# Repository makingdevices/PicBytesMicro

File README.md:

<!-- Improved compatibility of back to top link: See: https://github.com/othneildrew/Best-README-Template/pull/73 -->

<!--
*** Thanks for checking out the Best-README-Template. If you have a suggestion
*** that would make this better, please fork the repo and create a pull request
*** or simply open an issue with the tag "enhancement".
*** Don't forget to give the project a star!
*** Thanks again! Now go create something AMAZING! :D
-->

<!-- PROJECT SHIELDS -->
<!--
*** I'm using markdown "reference style" links for readability.
*** Reference links are enclosed in brackets [ ] instead of parentheses ( ).
*** See the bottom of this document for the declaration of the reference variables
*** for contributors-url, forks-url, etc. This is an optional, concise syntax you may use.
*** https://www.markdownguide.org/basic-syntax/#reference-style-links
-->
[![Instagram][ig-shield]][ig-url]
[![PCBWAY][sponsor-shield]][sponsor-url]
[![Stargazers][stars-shield]][stars-url]
[![Issues][issues-shield]][issues-url]
[![LinkedIn][linkedin-shield]][linkedin-url]

<!-- PROJECT LOGO -->
<br />
<div align="center">

<h3 align="center">Making Devices</h3>

  <p align="center">
    Open Source projects where we struggle with engineering, electronics, coding and who knows what else... Pic Bytes Micro is a 8-bit console based in the PIC18F4550 with an analog LED matrix as the screen.
  </p>
</div>

<!-- TABLE OF CONTENTS -->
<details>
  <summary>Table of Contents</summary>
  <ol>
    <li>
      <a href="#about-the-project">About The Project</a>
      <ul>
        <li><a href="#built-with">Built With</a></li>
      </ul>
    </li>
    <li>
      <a href="#Build-one">Build one</a>
      <ul>
      </ul>
    </li>
    <li><a href="#usage">Usage</a></li>
    <li><a href="#roadmap">Roadmap</a></li>
    <li><a href="#license">License</a></li>
    <li><a href="#contact">Contact</a></li>
    <li><a href="#Sponsor">Sponsor</a></li>
  </ol>
</details>

<!-- ABOUT THE PROJECT -->
## About The Project

[![Bytes Counter Shot][product-screenshot]](https://makingdevices.com/PicBytesMicro)

Pic Bytes Micro was born to explore the capabilities of C language inside the PIC18F4550, as I wanted to test if the 8bit microcontroller was able to run some old games such tetris, snake or arkanoid. To maintain the old-fashion look of the project, the screen is made by 16x10 matrix of LEDs, controlled by individual transistors and the IO pins of the PIC. In addition, sounds and a rechargable battery will be added to the device.

<p align="right">(<a href="#readme-top">back to top</a>)</p>

### Built With

[![Microcontroller][PIC]][PIC-url]
[![MPLAB C][MPLAB-C]][MPLAB-C-url]
[![Kicad][kicad-shield]][kicad-url]
[![SPONSOR][wurth-icon]][sponsor-url-wurth]
[![SPONSOR][sponsor-icon]][sponsor-url]

<p align="right">(<a href="#readme-top">back to top</a>)</p>

<!-- GETTING STARTED -->

## Build one
The project is finished and no further development will be made. The device is safe, stable and It was tested. 

1. Get the gerber files for the latest version: [V1.25](/Gerber/PicBytesMicroV1.25.zip) 
2. Send them to a PCB manufacturer ([Our Sponsor is PCBWAY][sponsor-url])
3. You can read the [schematics](/output_files/PicBytesMicro_schematic_V1.25.pdf) 
4. [The firmware is available on the repo](/Simulation%26Firmware) 
5. For most of the components, you can reach to [Würth Elektronik, our sponsor for electronic components](https://www.we-online.com/en) 

<p align="right">(<a href="#readme-top">back to top</a>)</p>

<!-- USAGE EXAMPLES -->
## Usage

Instructions of use:

- When turn on, a menu is shown to select between the available games.
- Once you have played a game, a score board will appear everytime you open the game.
- You have a setting menu to turn-off the init splash and the sound.
- If you leave the console one minute without touching the buttons, it will turn into sleep mode.
- Enjoy!

<p align="right">(<a href="#readme-top">back to top</a>)</p>

<!-- ROADMAP -->
## Roadmap

- [x] Solder the prototype
- [x] Test the LCD of the prototype
- [x] Design a PCB
  - [x] Add rechargeable battery
  - [x] Add USB communication if possible.
  - [x] Add sound control with the buzzers
  - [x] Develop Snake game
  - [x] Develop Tetris game
  - [x] Develop Arkanoid game
  - [x] Score board
  - [x] Sleep Mode
- [x] Validate the design

See the [open issues](https://github.com/makingdevices/PicBytesMicro/issues) for a full list of proposed features (and known issues).

State: Project <b>FINISHED</b> - 22/05/2024

Priority: <b>Medium</b>

<p align="right">(<a href="#readme-top">back to top</a>)</p>

<!-- LICENSE -->
## License

Distributed under three licenses:
- [Hardware](/License/HW_cern_ohl_s_v2.pdf)
- [Software](/License/SW_GPLv3.0.txt)
- [Documentation](/License/Documentation_CC-BY-SA-4.0.txt)

OSHWA License: [ES000047](https://certification.oshwa.org/es000047.html)

[![GPL v3 License][license-shield]][license-url] 
<p align="right">(<a href="#readme-top">back to top</a>)</p>

<!-- CONTACT -->
## Contact

Making Devices - [@MakingDevices](https://www.instagram.com/makingdevices/)

Project Link: [https://github.com/makingdevices/PicBytesMicro](https://github.com/makingdevices/PicBytesMicro/)

Other Links: [LinkTree](https://makingdevices.com/links/)

<!-- Sponsor -->
## Sponsors - Würth Elektronik

[Wurth Elektronik](https://www.we-online.com/en) is one of the leading manufacturers of electronic and electromechanical components. The best I can say about them is to show you some pictures: All the LEDs from the board are from them. They also have buttons, resistors and capacitors that we use in all our PCBs. They also have some design kits with a lifetime refill which are amazing for makers and business so you can prototype on the go with a huge variety of components!

[![Sponsor Shot][sponsor-wurth-1]][sponsor-url-wurth]
[![Sponsor Shot][sponsor-wurth-3]][sponsor-url-wurth]

## PCBWAY

[PCBWAY](https://www.pcbway.com/?from=makingdevices) is the most professional PCB manufacturer for prototyping and low-volume production to work with in the world. With more than a decade in the field, They are committed to meeting the needs of their customers from different industries in terms of quality, delivery, cost-effectiveness and any other demanding requests. As Sponsor of Making Devices, they will be in charge of all the PCBs for MDV, allowing both of us to grow together in a long term partnership. We hope you take them into account for your both personal and professional prototypes or products.

[![Sponsor Shot][sponsor-pcb-1]][sponsor-url]
[![Sponsor Shot][sponsor-pcb-2]][sponsor-url]

<p align="right">(<a href="#readme-top">back to top</a>)</p>

<!-- MARKDOWN LINKS & IMAGES -->
<!-- https://www.markdownguide.org/basic-syntax/#reference-style-links -->
[contributors-shield]: https://img.shields.io/github/contributors/makingdevices/PicBytesMicro.svg?style=for-the-badge
[contributors-url]: https://github.com/makingdevices/PicBytesMicro/graphs/contributors
[forks-shield]: https://img.shields.io/github/forks/makingdevices/PicBytesMicro.svg?style=for-the-badge
[forks-url]: https://github.com/makingdevices/PicBytesMicro/network/members
[stars-shield]: https://img.shields.io/github/stars/makingdevices/PicBytesMicro.svg?style=for-the-badge
[stars-url]: https://github.com/makingdevices/PicBytesMicro/stargazers
[issues-shield]: https://img.shields.io/github/issues/makingdevices/PicBytesMicro.svg?style=for-the-badge
[issues-url]: https://github.com/makingdevices/PicBytesMicro/issues
[license-shield]: /images/license.png
[license-url]: https://github.com/makingdevices/PicBytesMicro/tree/main/License
[linkedin-shield]: https://img.shields.io/badge/-LinkedIn-black.svg?style=for-the-badge&logo=linkedin&colorB=555
[linkedin-url]: https://www.linkedin.com/company/making-devices/
[sponsor-shield]: https://img.shields.io/badge/SPONSOR-PCBWAY-black.svg?style=for-the-badge&colorB=1200
[sponsor-url]: https://www.pcbway.com/?from=makingdevices
[sponsor-screenshot]: /images/PCB_sponsor.png
[sponsor-pcb-1]: /images/picbytesmicro_pcb1.jpg
[sponsor-pcb-2]: /images/picbytesmicro_pcb2.jpg
[sponsor-wurth-1]: /images/wurth_1.JPG
[sponsor-wurth-3]: /images/wurth_3.jpg
[sponsor-url-wurth]: https://www.we-online.com/en
[product-screenshot]: images/screenshot.jpg
[PIC]: https://img.shields.io/badge/PIC18LF4550-000000?style=for-the-badge
[PIC-url]: https://ww1.microchip.com/downloads/aemDocuments/documents/OTH/ProductDocuments/DataSheets/39632e.pdf
[kicad-shield]: https://img.shields.io/badge/kicad-0b03fc?style=for-the-badge&logo=kicad&logoColor=white
[kicad-url]: https://www.kicad.org/
[YT-screenshot]: images/YT_assembly.PNG
[sponsor-icon]:  https://img.shields.io/badge/-PCBWAY-black.svg?style=for-the-badge&colorB=1200
[ig-shield]: https://img.shields.io/badge/instagram-a83297?style=for-the-badge&logo=instagram&logoColor=white
[ig-url]: https://www.instagram.com/makingdevices/
[MPLAB-C]: https://img.shields.io/badge/MPLAB%20C18-DD0031?style=for-the-badge&logo=C&logoColor=white
[wurth-icon]: https://img.shields.io/badge/Wurth%20elektronik-FF0031?style=for-the-badge&logoColor=white
[MPLAB-C-url]: https://www.microchip.com/en-us/development-tool/SW006011
[Svelte.dev]: https://img.shields.io/badge/Svelte-4A4A55?style=for-the-badge&logo=svelte&logoColor=FF3E00
[Svelte-url]: https://svelte.dev/
[Laravel.com]: https://img.shields.io/badge/Laravel-FF2D20?style=for-the-badge&logo=laravel&logoColor=white
[Laravel-url]: https://laravel.com
[Bootstrap.com]: https://img.shields.io/badge/Bootstrap-563D7C?style=for-the-badge&logo=bootstrap&logoColor=white
[Bootstrap-url]: https://getbootstrap.com
[JQuery.com]: https://img.shields.io/badge/jQuery-0769AD?style=for-the-badge&logo=jquery&logoColor=white
[JQuery-url]: https://jquery.com

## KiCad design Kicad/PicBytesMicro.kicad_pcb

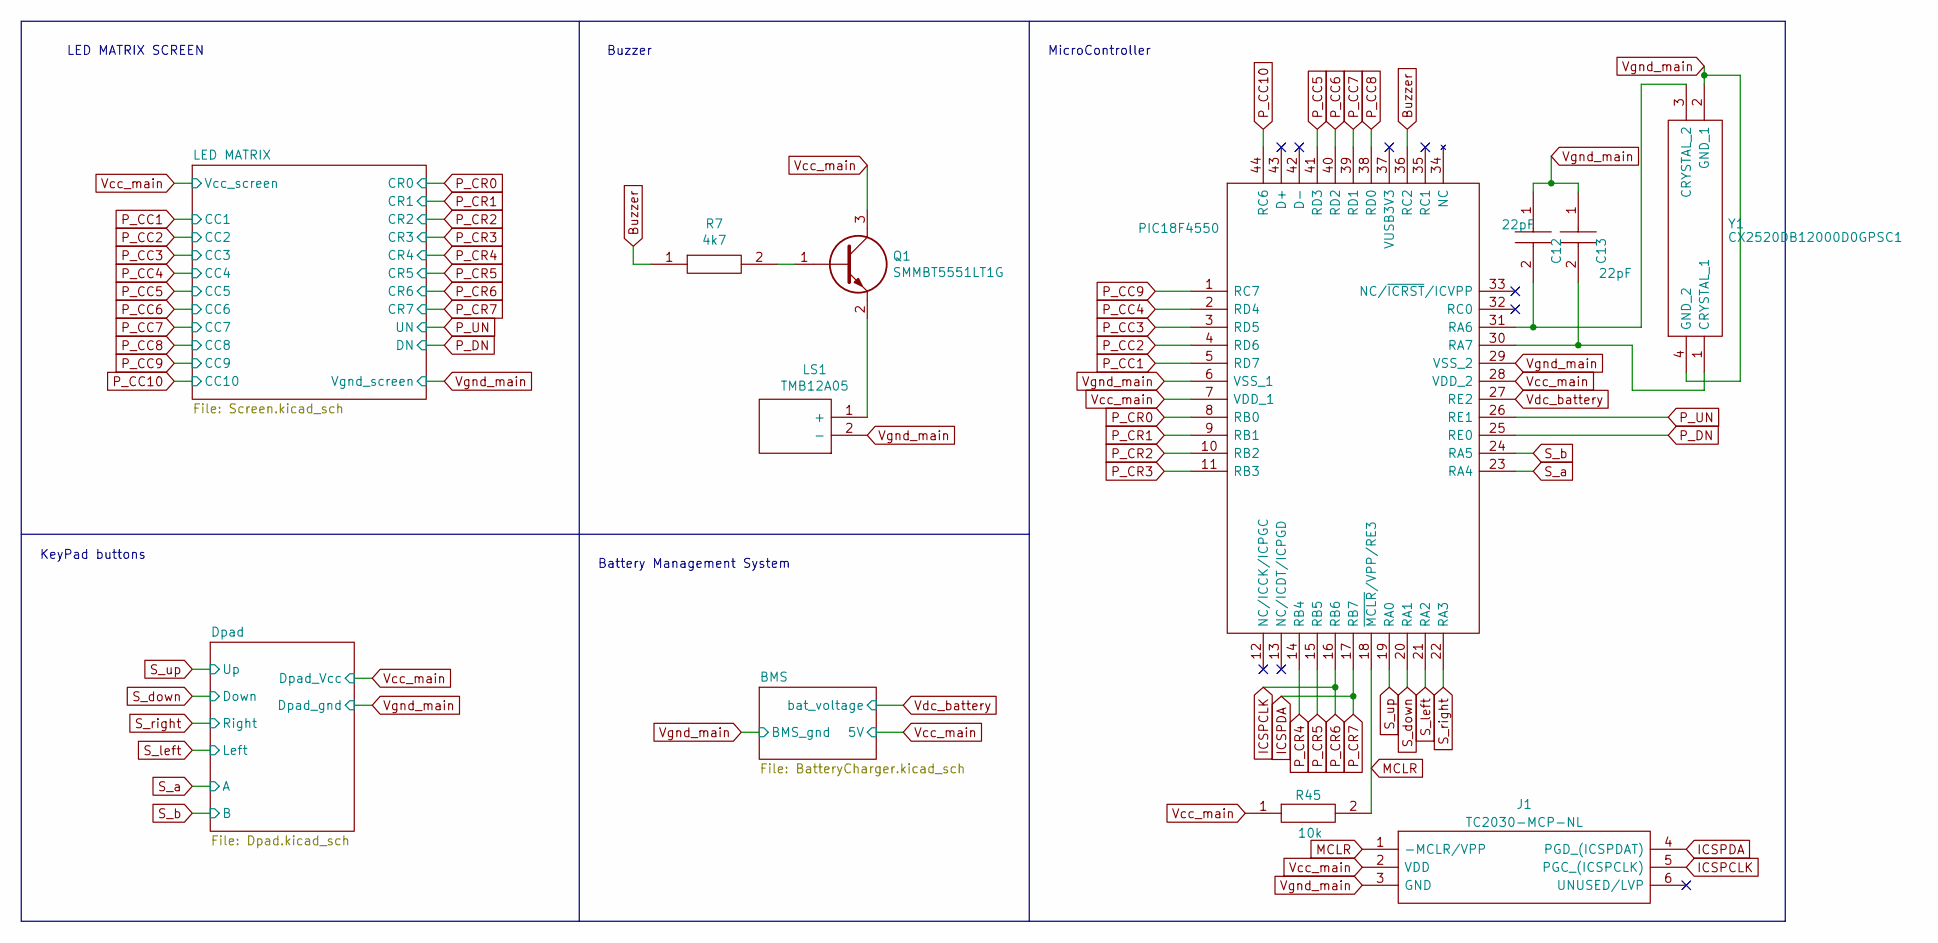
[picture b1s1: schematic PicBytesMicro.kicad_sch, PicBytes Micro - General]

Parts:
C12, C13: 22pF; CAPC2012X145N; Manufacturer_Part_Number GCG21BR71H154KA01K
J1: TC2030-MCP-NL; Manufacturer_Part_Number TC2030-MCP-NL
LS1: TMB12A05; Manufacturer_Part_Number TMB12A05
PIC18F4550: PIC18F4550-I_PT; QFP80P1200X1200X120-44N; Manufacturer_Part_Number PIC18F45K50-I/PT
Q1: SMMBT5551LT1G; SOT96P237X111-3N; Manufacturer_Part_Number SMMBT5551LT1G
R7: 4k7; RESC2012X65N; Manufacturer_Part_Number KTR10EZPF4220
R45: 10k; RESC2012X65N; Manufacturer_Part_Number KTR10EZPF4220
Y1: CX2520DB12000D0GPSC1; Manufacturer_Part_Number CX2520DB12000D0GPSC1

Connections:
Buzzer: PIC18F4550.36 (RC2), R7.1
ICSPCLK: J1.5 (PGC_(ICSPCLK)), PIC18F4550.16 (RB6); also elsewhere on the board
ICSPDA: J1.4 (PGD_(ICSPDAT)), PIC18F4550.17 (RB7); also elsewhere on the board
MCLR: J1.1 (-MCLR/VPP), PIC18F4550.18 (~MCLR/VPP/RE3), R45.2
unnamed: LS1.1 (+), Q1.2
unnamed: C12.2, PIC18F4550.31 (RA6), Y1.3 (CRYSTAL_2)
unnamed: C13.2, PIC18F4550.30 (RA7), Y1.1 (CRYSTAL_1)
unnamed: Q1.1, R7.2
P_CC1: PIC18F4550.5 (RD7); also elsewhere on the board
P_CC2: PIC18F4550.4 (RD6); also elsewhere on the board
P_CC3: PIC18F4550.3 (RD5); also elsewhere on the board
P_CC4: PIC18F4550.2 (RD4); also elsewhere on the board
P_CC5: PIC18F4550.41 (RD3); also elsewhere on the board
P_CC6: PIC18F4550.40 (RD2); also elsewhere on the board
P_CC7: PIC18F4550.39 (RD1); also elsewhere on the board
P_CC8: PIC18F4550.38 (RD0); also elsewhere on the board
P_CC9: PIC18F4550.1 (RC7); also elsewhere on the board
P_CC10: PIC18F4550.44 (RC6); also elsewhere on the board
P_CR0: PIC18F4550.8 (RB0); also elsewhere on the board
P_CR1: PIC18F4550.9 (RB1); also elsewhere on the board
P_CR2: PIC18F4550.10 (RB2); also elsewhere on the board
P_CR3: PIC18F4550.11 (RB3); also elsewhere on the board
P_CR4: PIC18F4550.14 (RB4); also elsewhere on the board
P_CR5: PIC18F4550.15 (RB5); also elsewhere on the board
P_DN: PIC18F4550.25 (RE0); also elsewhere on the board
P_UN: PIC18F4550.26 (RE1); also elsewhere on the board
S_a: PIC18F4550.23 (RA4); also elsewhere on the board
S_b: PIC18F4550.24 (RA5); also elsewhere on the board
S_down: PIC18F4550.20 (RA1); also elsewhere on the board
S_left: PIC18F4550.21 (RA2); also elsewhere on the board
S_right: PIC18F4550.22 (RA3); also elsewhere on the board
S_up: PIC18F4550.19 (RA0); also elsewhere on the board
Vcc_main: J1.2 (VDD), PIC18F4550.7 (VDD_1), PIC18F4550.28 (VDD_2), Q1.3, R45.1; also elsewhere on the board
Vdc_battery: PIC18F4550.27 (RE2); also elsewhere on the board
Vgnd_main: C12.1, C13.1, J1.3 (GND), LS1.2 (-), PIC18F4550.6 (VSS_1), PIC18F4550.29 (VSS_2), Y1.2 (GND_1), Y1.4 (GND_2); also elsewhere on the board

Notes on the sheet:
MicroController
KeyPad buttons
Battery Management System
LED MATRIX SCREEN
Buzzer

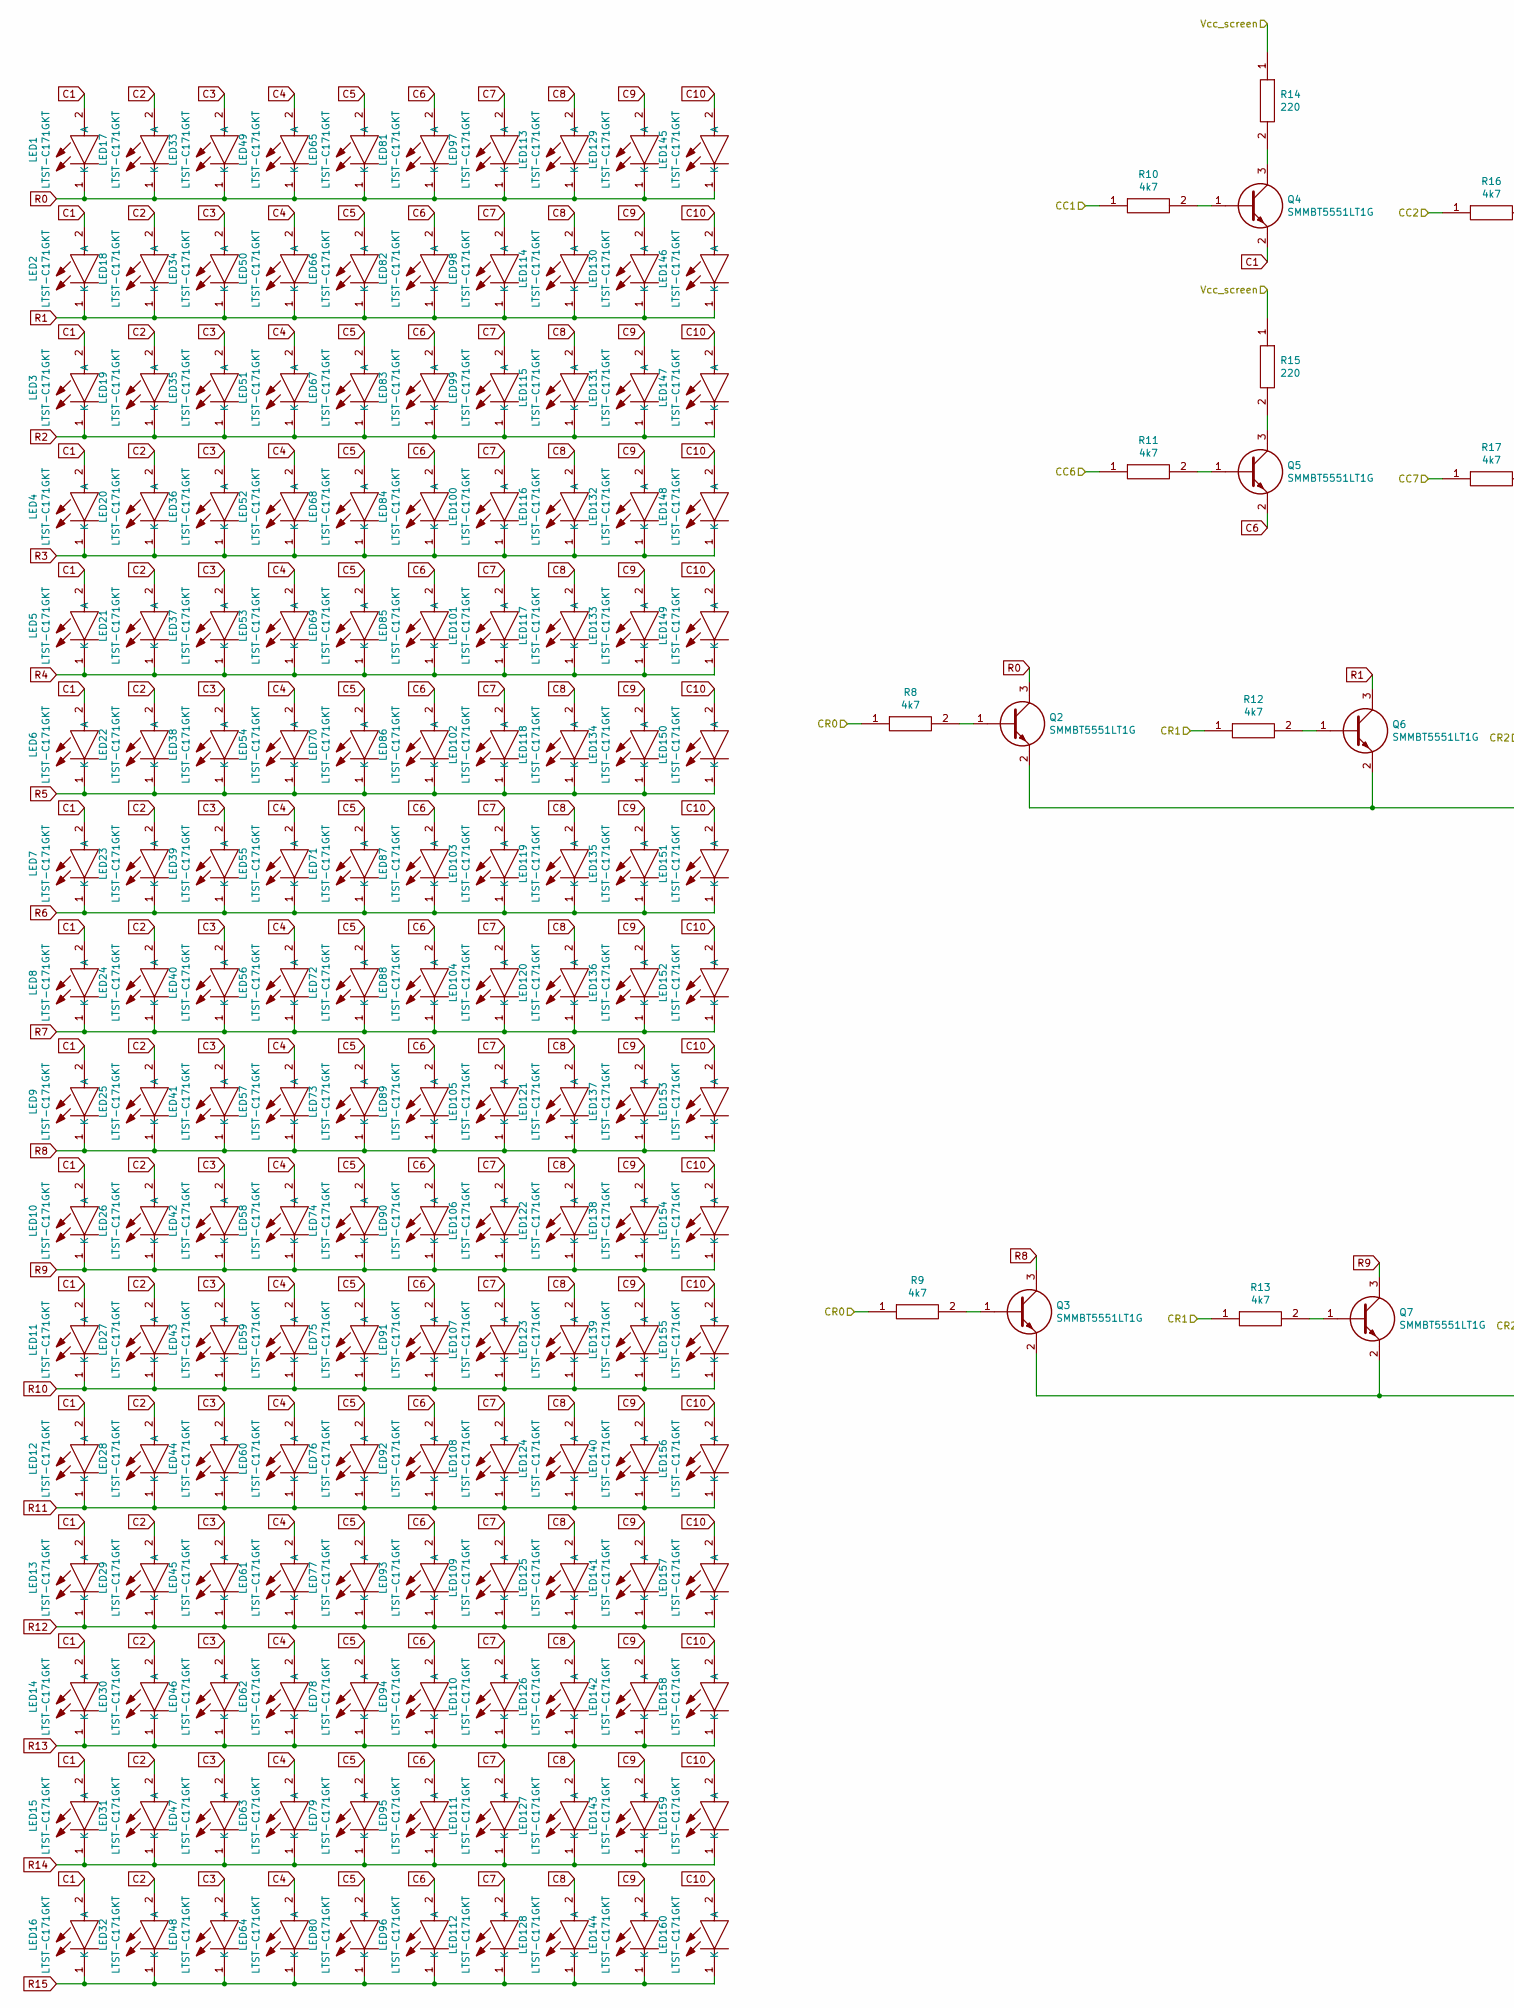
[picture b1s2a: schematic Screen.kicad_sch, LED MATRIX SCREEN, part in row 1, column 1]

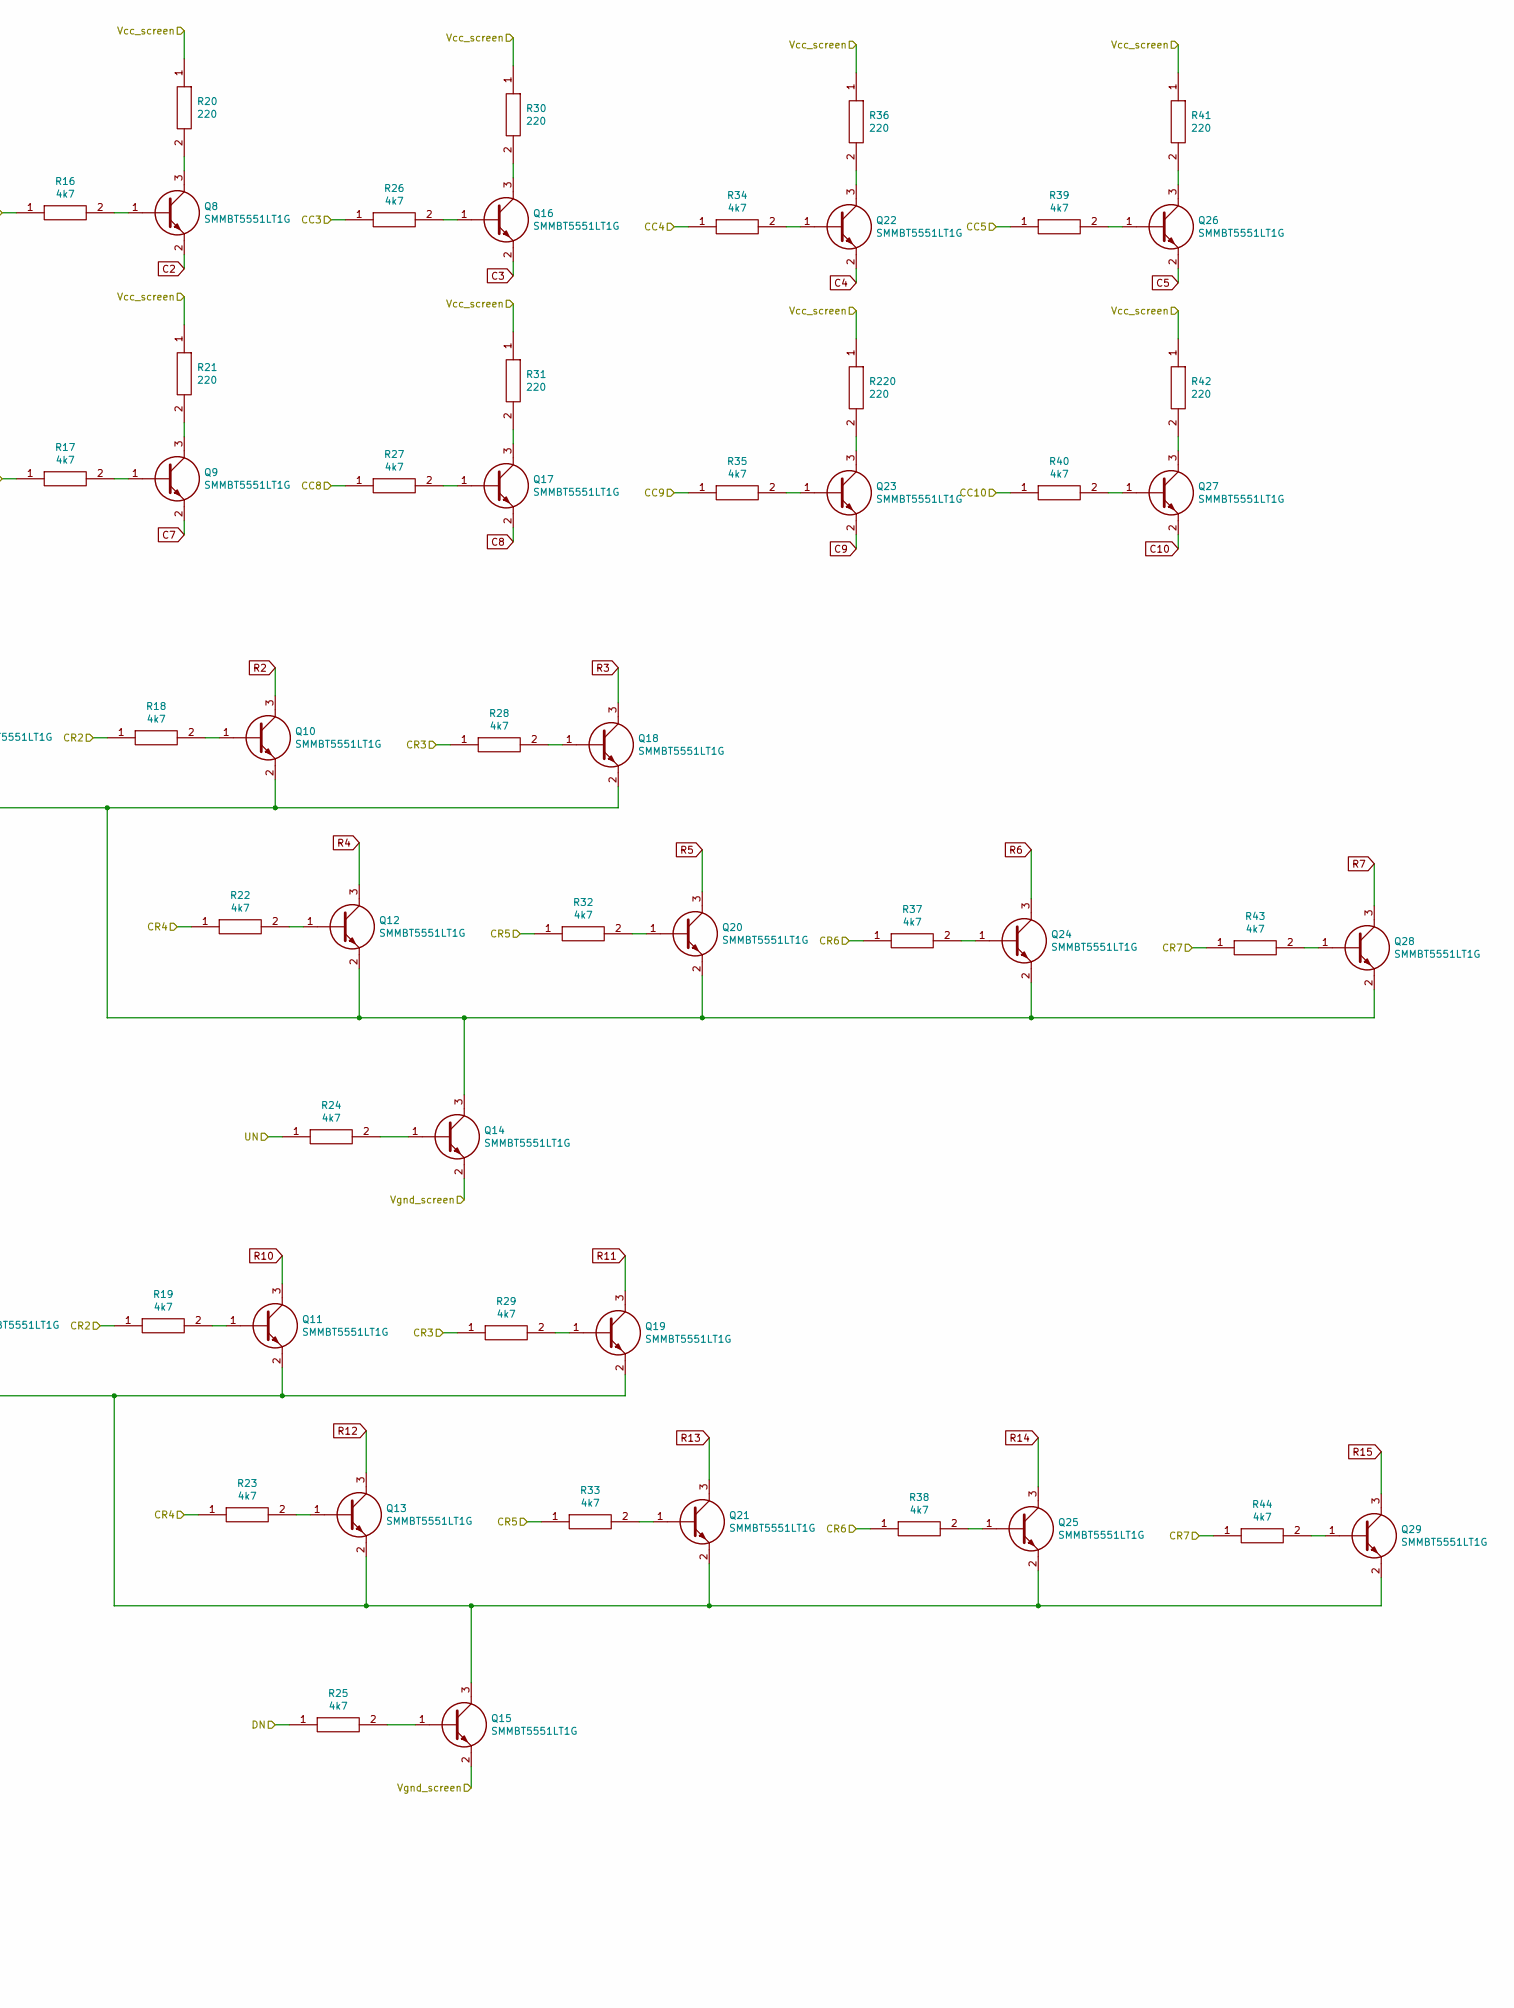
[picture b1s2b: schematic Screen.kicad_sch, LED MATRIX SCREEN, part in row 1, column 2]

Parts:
LED1, LED2, LED3, LED4, LED5, LED6, LED7, LED8, LED9, LED10, LED11, LED12, LED13, LED14, LED15, LED16, LED17, LED18, LED19, LED20, LED21, LED22, LED23, LED24, LED25, LED26, LED27, LED28, LED29, LED30, LED31, LED32, LED33, LED34, LED35, LED36, LED37, LED38, LED39, LED40, LED41, LED42, LED43, LED44, LED45, LED46, LED47, LED48, LED49, LED50, LED51, LED52, LED53, LED54, LED55, LED56, LED57, LED58, LED59, LED60, LED61, LED62, LED63, LED64, LED65, LED66, LED67, LED68, LED69, LED70, LED71, LED72, LED73, LED74, LED75, LED76, LED77, LED78, LED79, LED80, LED81, LED82, LED83, LED84, LED85, LED86, LED87, LED88, LED89, LED90, LED91, LED92, LED93, LED94, LED95, LED96, LED97, LED98, LED99, LED100, LED101, LED102, LED103, LED104, LED105, LED106, LED107, LED108, LED109, LED110, LED111, LED112, LED113, LED114, LED115, LED116, LED117, LED118, LED119, LED120, LED121, LED122, LED123, LED124, LED125, LED126, LED127, LED128, LED129, LED130, LED131, LED132, LED133, LED134, LED135, LED136, LED137, LED138, LED139, LED140, LED141, LED142, LED143, LED144, LED145, LED146, LED147, LED148, LED149, LED150, LED151, LED152, LED153, LED154, LED155, LED156, LED157, LED158, LED159, LED160: LTST-C171GKT; LEDC2012X90N; Manufacturer_Part_Number LTST-C171GKT
Q2, Q3, Q4, Q5, Q6, Q7, Q8, Q9, Q10, Q11, Q12, Q13, Q14, Q15, Q16, Q17, Q18, Q19, Q20, Q21, Q22, Q23, Q24, Q25, Q26, Q27, Q28, Q29: SMMBT5551LT1G; SOT96P237X111-3N; Manufacturer_Part_Number SMMBT5551LT1G
R8, R9, R10, R11, R12, R13, R16, R17, R18, R19, R22, R23, R24, R25, R26, R27, R28, R29, R32, R33, R34, R35, R37, R38, R39, R40, R43, R44: 4k7; RESC2012X65N; Manufacturer_Part_Number KTR10EZPF4220
R14, R15, R20, R21, R30, R31, R36, R41, R42, R220: 220; RESC2012X65N; Manufacturer_Part_Number KTR10EZPF4220

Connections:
C1: LED1.2 (A), LED2.2 (A), LED3.2 (A), LED4.2 (A), LED5.2 (A), LED6.2 (A), LED7.2 (A), LED8.2 (A), LED9.2 (A), LED10.2 (A), LED11.2 (A), LED12.2 (A), LED13.2 (A), LED14.2 (A), LED15.2 (A), LED16.2 (A), Q4.2
C2: LED17.2 (A), LED18.2 (A), LED19.2 (A), LED20.2 (A), LED21.2 (A), LED22.2 (A), LED23.2 (A), LED24.2 (A), LED25.2 (A), LED26.2 (A), LED27.2 (A), LED28.2 (A), LED29.2 (A), LED30.2 (A), LED31.2 (A), LED32.2 (A), Q8.2
C3: LED33.2 (A), LED34.2 (A), LED35.2 (A), LED36.2 (A), LED37.2 (A), LED38.2 (A), LED39.2 (A), LED40.2 (A), LED41.2 (A), LED42.2 (A), LED43.2 (A), LED44.2 (A), LED45.2 (A), LED46.2 (A), LED47.2 (A), LED48.2 (A), Q16.2
C4: LED49.2 (A), LED50.2 (A), LED51.2 (A), LED52.2 (A), LED53.2 (A), LED54.2 (A), LED55.2 (A), LED56.2 (A), LED57.2 (A), LED58.2 (A), LED59.2 (A), LED60.2 (A), LED61.2 (A), LED62.2 (A), LED63.2 (A), LED64.2 (A), Q22.2
C5: LED65.2 (A), LED66.2 (A), LED67.2 (A), LED68.2 (A), LED69.2 (A), LED70.2 (A), LED71.2 (A), LED72.2 (A), LED73.2 (A), LED74.2 (A), LED75.2 (A), LED76.2 (A), LED77.2 (A), LED78.2 (A), LED79.2 (A), LED80.2 (A), Q26.2
C6: LED81.2 (A), LED82.2 (A), LED83.2 (A), LED84.2 (A), LED85.2 (A), LED86.2 (A), LED87.2 (A), LED88.2 (A), LED89.2 (A), LED90.2 (A), LED91.2 (A), LED92.2 (A), LED93.2 (A), LED94.2 (A), LED95.2 (A), LED96.2 (A), Q5.2
C7: LED97.2 (A), LED98.2 (A), LED99.2 (A), LED100.2 (A), LED101.2 (A), LED102.2 (A), LED103.2 (A), LED104.2 (A), LED105.2 (A), LED106.2 (A), LED107.2 (A), LED108.2 (A), LED109.2 (A), LED110.2 (A), LED111.2 (A), LED112.2 (A), Q9.2
C8: LED113.2 (A), LED114.2 (A), LED115.2 (A), LED116.2 (A), LED117.2 (A), LED118.2 (A), LED119.2 (A), LED120.2 (A), LED121.2 (A), LED122.2 (A), LED123.2 (A), LED124.2 (A), LED125.2 (A), LED126.2 (A), LED127.2 (A), LED128.2 (A), Q17.2
C9: LED129.2 (A), LED130.2 (A), LED131.2 (A), LED132.2 (A), LED133.2 (A), LED134.2 (A), LED135.2 (A), LED136.2 (A), LED137.2 (A), LED138.2 (A), LED139.2 (A), LED140.2 (A), LED141.2 (A), LED142.2 (A), LED143.2 (A), LED144.2 (A), Q23.2
C10: LED145.2 (A), LED146.2 (A), LED147.2 (A), LED148.2 (A), LED149.2 (A), LED150.2 (A), LED151.2 (A), LED152.2 (A), LED153.2 (A), LED154.2 (A), LED155.2 (A), LED156.2 (A), LED157.2 (A), LED158.2 (A), LED159.2 (A), LED160.2 (A), Q27.2
ICSPCLK: R37.1, R38.1; also elsewhere on the board
ICSPDA: R43.1, R44.1; also elsewhere on the board
unnamed: Q2.1, R8.2
unnamed: Q3.1, R9.2
unnamed: Q4.1, R10.2
unnamed: Q4.3, R14.2
unnamed: Q5.1, R11.2
unnamed: Q5.3, R15.2
unnamed: Q6.1, R12.2
unnamed: Q7.1, R13.2
unnamed: Q8.1, R16.2
unnamed: Q8.3, R20.2
unnamed: Q9.1, R17.2
unnamed: Q9.3, R21.2
unnamed: Q10.1, R18.2
unnamed: Q2.2, Q6.2, Q10.2, Q12.2, Q14.3, Q18.2, Q20.2, Q24.2, Q28.2
unnamed: Q11.1, R19.2
unnamed: Q3.2, Q7.2, Q11.2, Q13.2, Q15.3, Q19.2, Q21.2, Q25.2, Q29.2
unnamed: Q12.1, R22.2
unnamed: Q13.1, R23.2
unnamed: Q14.1, R24.2
unnamed: Q15.1, R25.2
unnamed: Q16.1, R26.2
unnamed: Q16.3, R30.2
unnamed: Q17.1, R27.2
unnamed: Q17.3, R31.2
unnamed: Q18.1, R28.2
unnamed: Q19.1, R29.2
unnamed: Q20.1, R32.2
unnamed: Q21.1, R33.2
unnamed: Q22.1, R34.2
unnamed: Q22.3, R36.2
unnamed: Q23.1, R35.2
unnamed: Q23.3, R220.2
unnamed: Q24.1, R37.2
unnamed: Q25.1, R38.2
unnamed: Q26.1, R39.2
unnamed: Q26.3, R41.2
unnamed: Q27.1, R40.2
unnamed: Q27.3, R42.2
unnamed: Q28.1, R43.2
unnamed: Q29.1, R44.2
P_CC1: R10.1; also elsewhere on the board
P_CC2: R16.1; also elsewhere on the board
P_CC3: R26.1; also elsewhere on the board
P_CC4: R34.1; also elsewhere on the board
P_CC5: R39.1; also elsewhere on the board
P_CC6: R11.1; also elsewhere on the board
P_CC7: R17.1; also elsewhere on the board
P_CC8: R27.1; also elsewhere on the board
P_CC9: R35.1; also elsewhere on the board
P_CC10: R40.1; also elsewhere on the board
P_CR0: R8.1, R9.1; also elsewhere on the board
P_CR1: R12.1, R13.1; also elsewhere on the board
P_CR2: R18.1, R19.1; also elsewhere on the board
P_CR3: R28.1, R29.1; also elsewhere on the board
P_CR4: R22.1, R23.1; also elsewhere on the board
P_CR5: R32.1, R33.1; also elsewhere on the board
P_DN: R25.1; also elsewhere on the board
P_UN: R24.1; also elsewhere on the board
R0: LED1.1 (K), LED17.1 (K), LED33.1 (K), LED49.1 (K), LED65.1 (K), LED81.1 (K), LED97.1 (K), LED113.1 (K), LED129.1 (K), LED145.1 (K), Q2.3
R1: LED2.1 (K), LED18.1 (K), LED34.1 (K), LED50.1 (K), LED66.1 (K), LED82.1 (K), LED98.1 (K), LED114.1 (K), LED130.1 (K), LED146.1 (K), Q6.3
R2: LED3.1 (K), LED19.1 (K), LED35.1 (K), LED51.1 (K), LED67.1 (K), LED83.1 (K), LED99.1 (K), LED115.1 (K), LED131.1 (K), LED147.1 (K), Q10.3
R3: LED4.1 (K), LED20.1 (K), LED36.1 (K), LED52.1 (K), LED68.1 (K), LED84.1 (K), LED100.1 (K), LED116.1 (K), LED132.1 (K), LED148.1 (K), Q18.3
R4: LED5.1 (K), LED21.1 (K), LED37.1 (K), LED53.1 (K), LED69.1 (K), LED85.1 (K), LED101.1 (K), LED117.1 (K), LED133.1 (K), LED149.1 (K), Q12.3
R5: LED6.1 (K), LED22.1 (K), LED38.1 (K), LED54.1 (K), LED70.1 (K), LED86.1 (K), LED102.1 (K), LED118.1 (K), LED134.1 (K), LED150.1 (K), Q20.3
R6: LED7.1 (K), LED23.1 (K), LED39.1 (K), LED55.1 (K), LED71.1 (K), LED87.1 (K), LED103.1 (K), LED119.1 (K), LED135.1 (K), LED151.1 (K), Q24.3
R7: LED8.1 (K), LED24.1 (K), LED40.1 (K), LED56.1 (K), LED72.1 (K), LED88.1 (K), LED104.1 (K), LED120.1 (K), LED136.1 (K), LED152.1 (K), Q28.3
R8: LED9.1 (K), LED25.1 (K), LED41.1 (K), LED57.1 (K), LED73.1 (K), LED89.1 (K), LED105.1 (K), LED121.1 (K), LED137.1 (K), LED153.1 (K), Q3.3
R9: LED10.1 (K), LED26.1 (K), LED42.1 (K), LED58.1 (K), LED74.1 (K), LED90.1 (K), LED106.1 (K), LED122.1 (K), LED138.1 (K), LED154.1 (K), Q7.3
R10: LED11.1 (K), LED27.1 (K), LED43.1 (K), LED59.1 (K), LED75.1 (K), LED91.1 (K), LED107.1 (K), LED123.1 (K), LED139.1 (K), LED155.1 (K), Q11.3
R11: LED12.1 (K), LED28.1 (K), LED44.1 (K), LED60.1 (K), LED76.1 (K), LED92.1 (K), LED108.1 (K), LED124.1 (K), LED140.1 (K), LED156.1 (K), Q19.3
R12: LED13.1 (K), LED29.1 (K), LED45.1 (K), LED61.1 (K), LED77.1 (K), LED93.1 (K), LED109.1 (K), LED125.1 (K), LED141.1 (K), LED157.1 (K), Q13.3
R13: LED14.1 (K), LED30.1 (K), LED46.1 (K), LED62.1 (K), LED78.1 (K), LED94.1 (K), LED110.1 (K), LED126.1 (K), LED142.1 (K), LED158.1 (K), Q21.3
R14: LED15.1 (K), LED31.1 (K), LED47.1 (K), LED63.1 (K), LED79.1 (K), LED95.1 (K), LED111.1 (K), LED127.1 (K), LED143.1 (K), LED159.1 (K), Q25.3
R15: LED16.1 (K), LED32.1 (K), LED48.1 (K), LED64.1 (K), LED80.1 (K), LED96.1 (K), LED112.1 (K), LED128.1 (K), LED144.1 (K), LED160.1 (K), Q29.3
Vcc_main: R14.1, R15.1, R20.1, R21.1, R30.1, R31.1, R36.1, R41.1, R42.1, R220.1; also elsewhere on the board
Vgnd_main: Q14.2, Q15.2; also elsewhere on the board

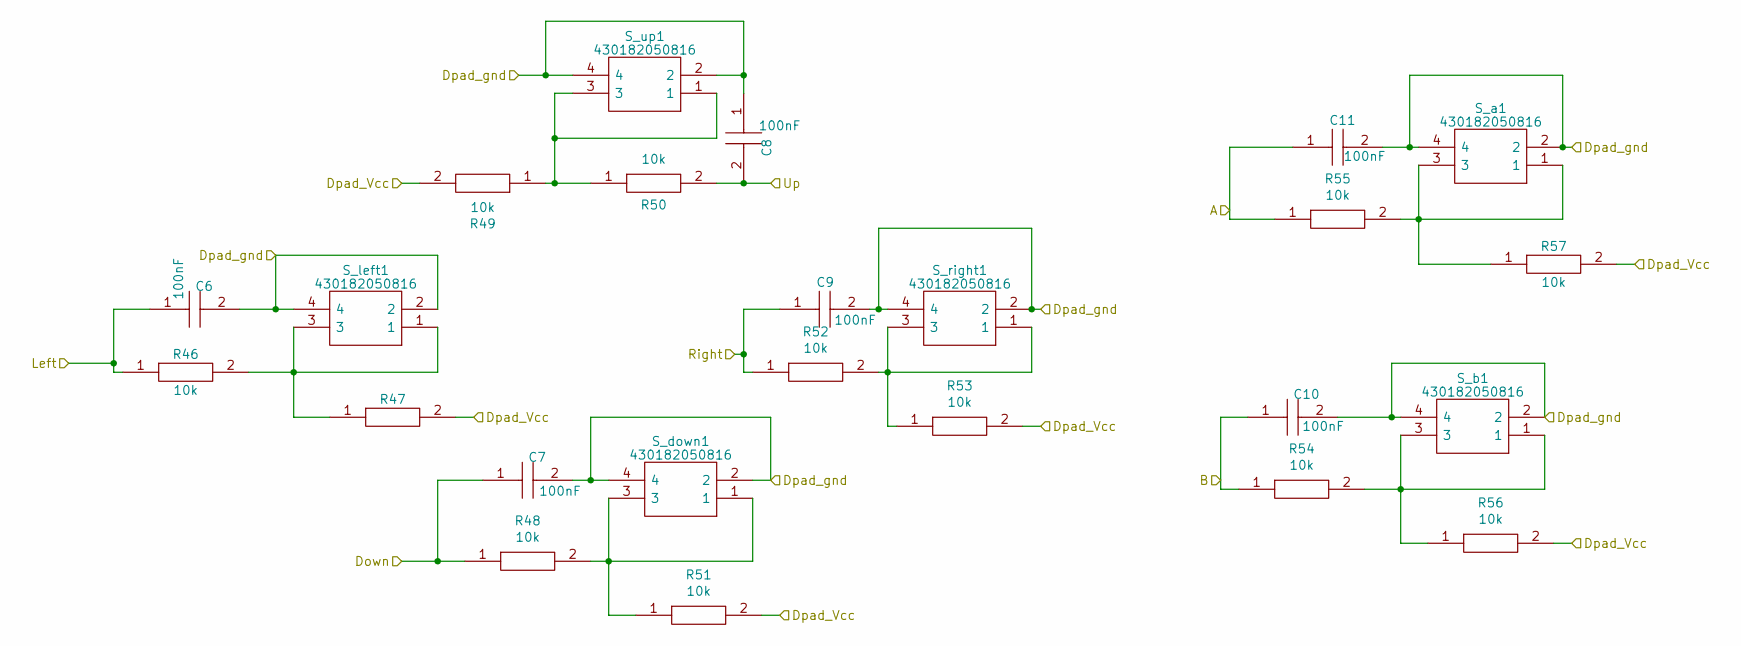
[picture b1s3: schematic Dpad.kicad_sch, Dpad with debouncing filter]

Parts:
C6, C7, C8, C9, C10, C11: 100nF; CAPC2012X140N; Manufacturer_Part_Number GCG21BR71H154KA01K
R46, R48, R49, R52, R54, R55: 10k; RESC2012X75N; Manufacturer_Part_Number KTR10EZPF4220
R47, R50, R51, R53, R56, R57: 10k; RESC2012X65N; Manufacturer_Part_Number KTR10EZPF4220
S_a1: 430182050816; 430182070816; Mouser Part Number 710-430182050816
S_b1: 430182050816; 430182070816; Mouser Part Number 710-430182050816
S_down1: 430182050816; 430182070816; Mouser Part Number 710-430182050816
S_left1: 430182050816; 430182070816; Mouser Part Number 710-430182050816
S_right1: 430182050816; 430182070816; Mouser Part Number 710-430182050816
S_up1: 430182050816; 430182070816; Mouser Part Number 710-430182050816

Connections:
unnamed: R46.2, R47.1, S_left1.1, S_left1.3
unnamed: R48.2, R51.1, S_down1.1, S_down1.3
unnamed: R49.1, R50.1, S_up1.1, S_up1.3
unnamed: R52.2, R53.1, S_right1.1, S_right1.3
unnamed: R54.2, R56.1, S_b1.1, S_b1.3
unnamed: R55.2, R57.1, S_a1.1, S_a1.3
S_a: C11.1, R55.1; also elsewhere on the board
S_b: C10.1, R54.1; also elsewhere on the board
S_down: C7.1, R48.1; also elsewhere on the board
S_left: C6.1, R46.1; also elsewhere on the board
S_right: C9.1, R52.1; also elsewhere on the board
S_up: C8.2, R50.2; also elsewhere on the board
Vcc_main: R47.2, R49.2, R51.2, R53.2, R56.2, R57.2; also elsewhere on the board
Vgnd_main: C6.2, C7.2, C8.1, C9.2, C10.2, C11.2, S_a1.2, S_a1.4, S_b1.2, S_b1.4, S_down1.2, S_down1.4, S_left1.2, S_left1.4, S_right1.2, S_right1.4, S_up1.2, S_up1.4; also elsewhere on the board
